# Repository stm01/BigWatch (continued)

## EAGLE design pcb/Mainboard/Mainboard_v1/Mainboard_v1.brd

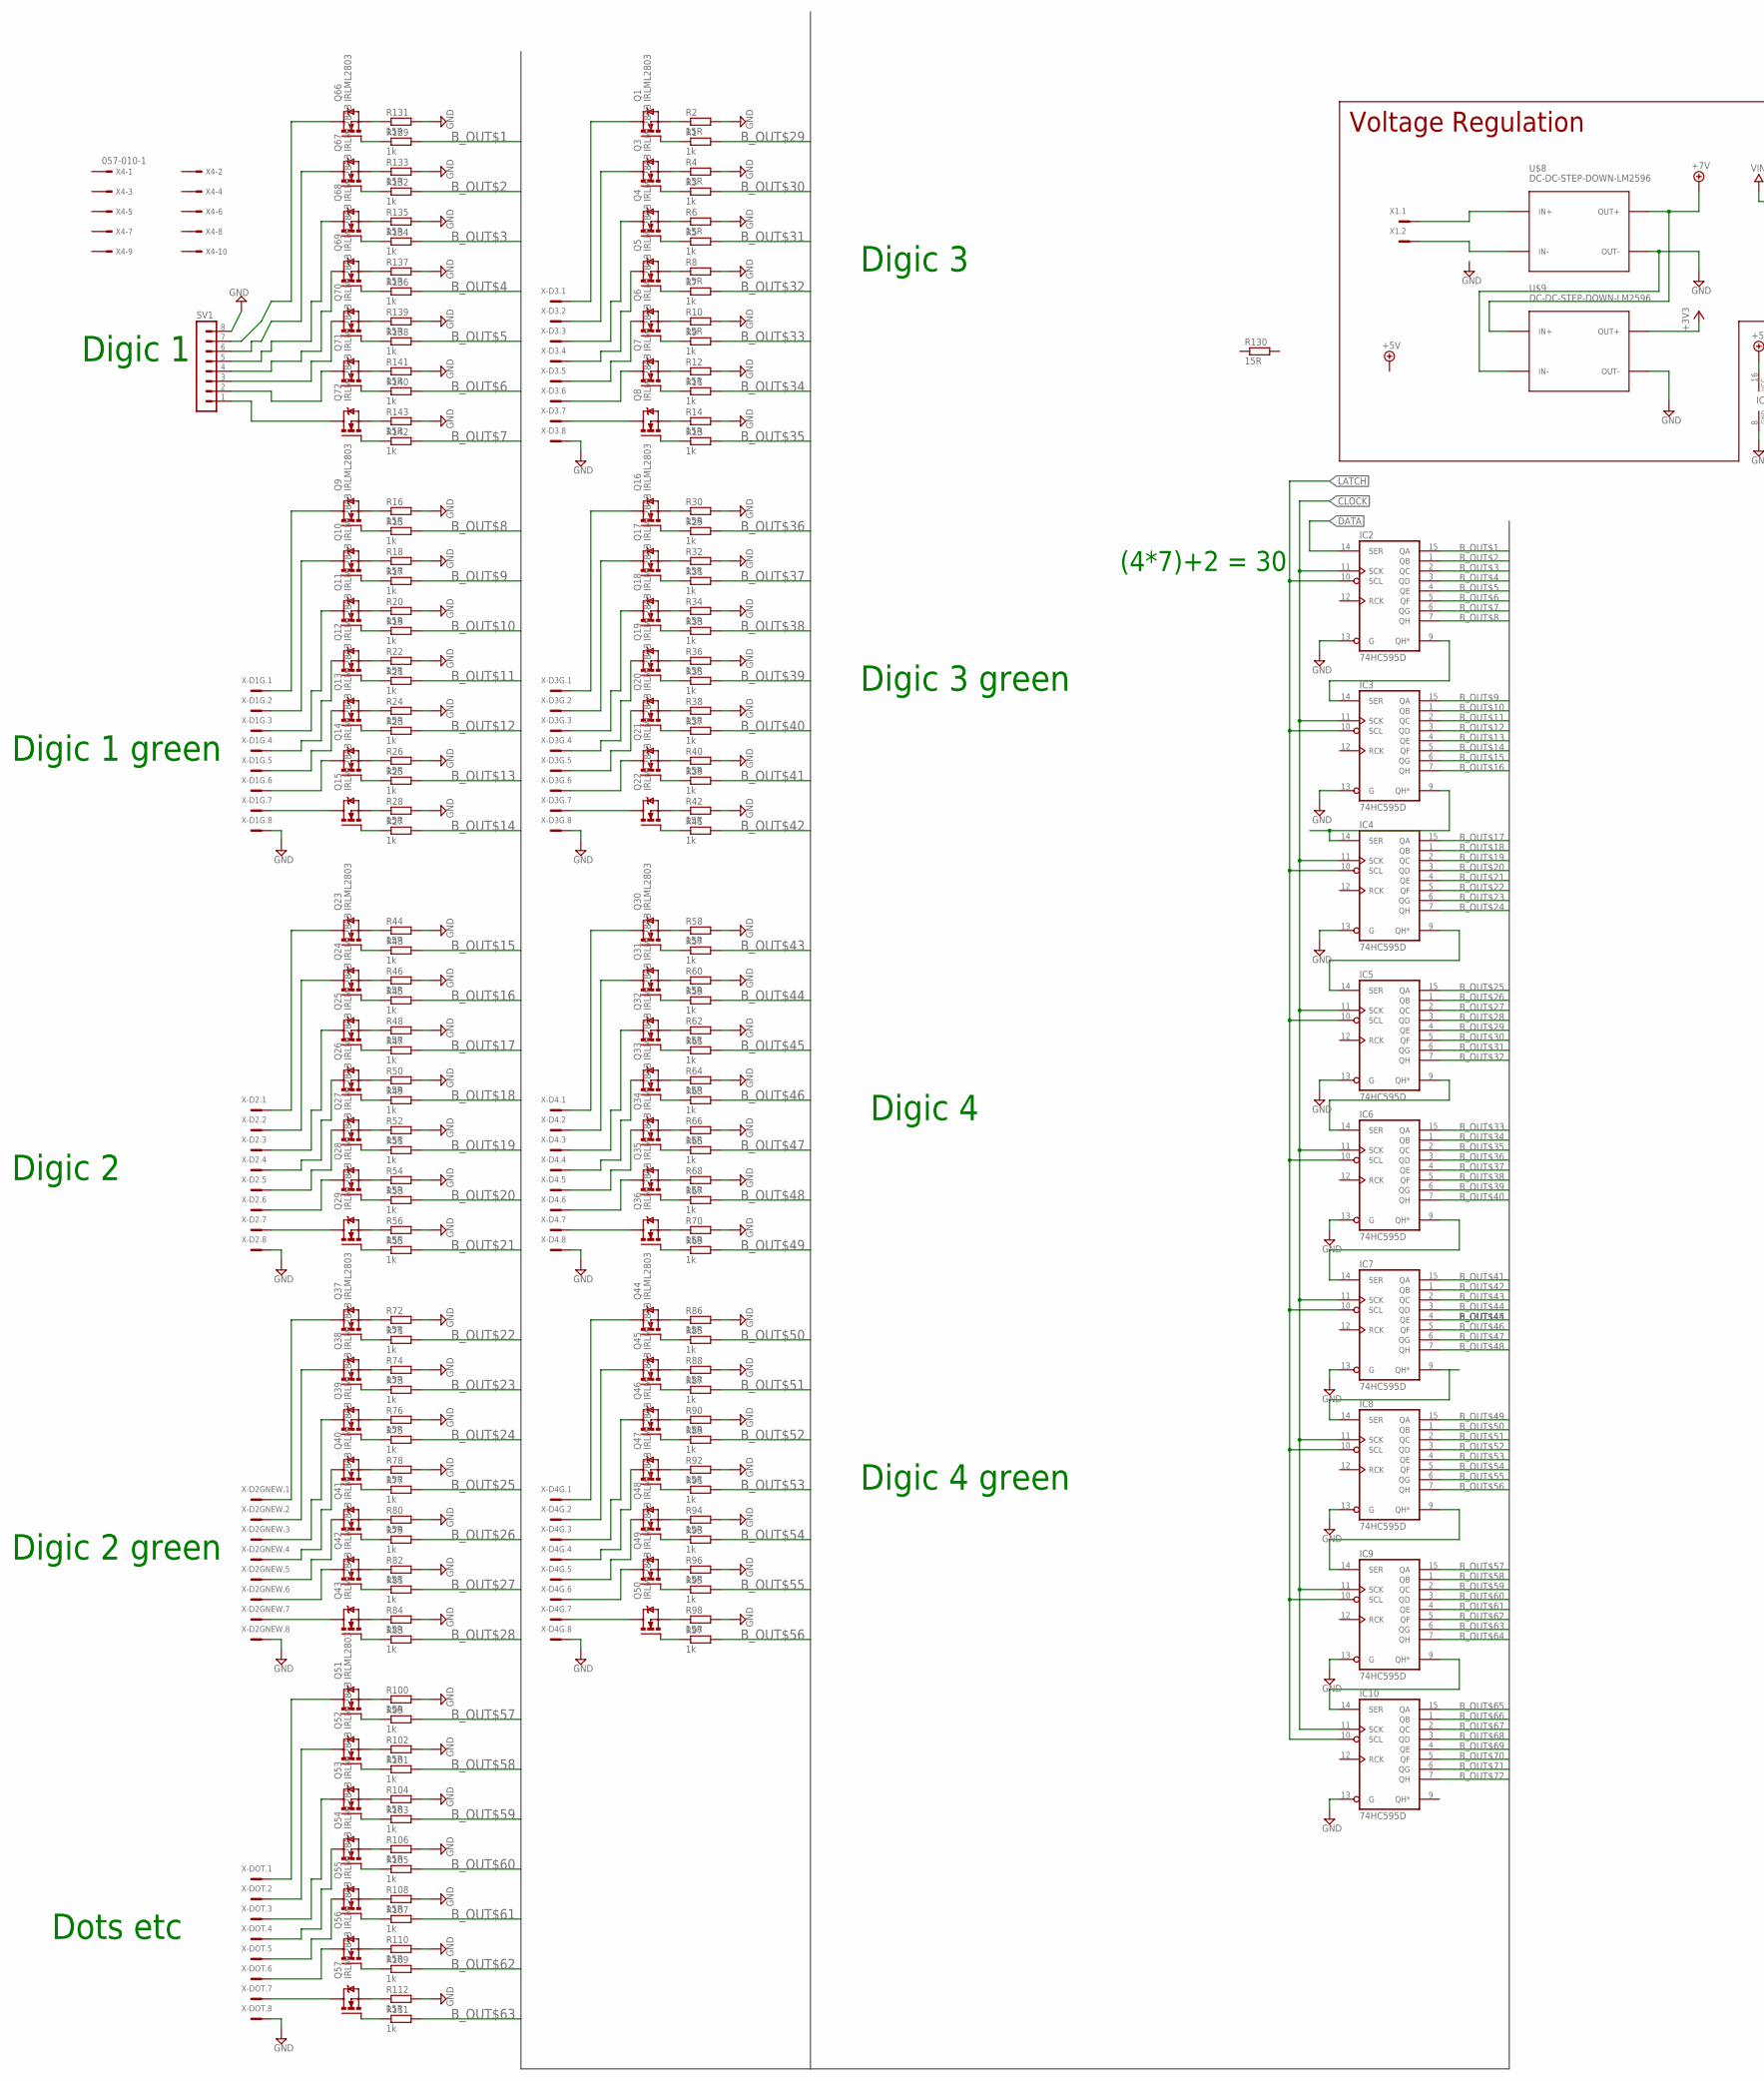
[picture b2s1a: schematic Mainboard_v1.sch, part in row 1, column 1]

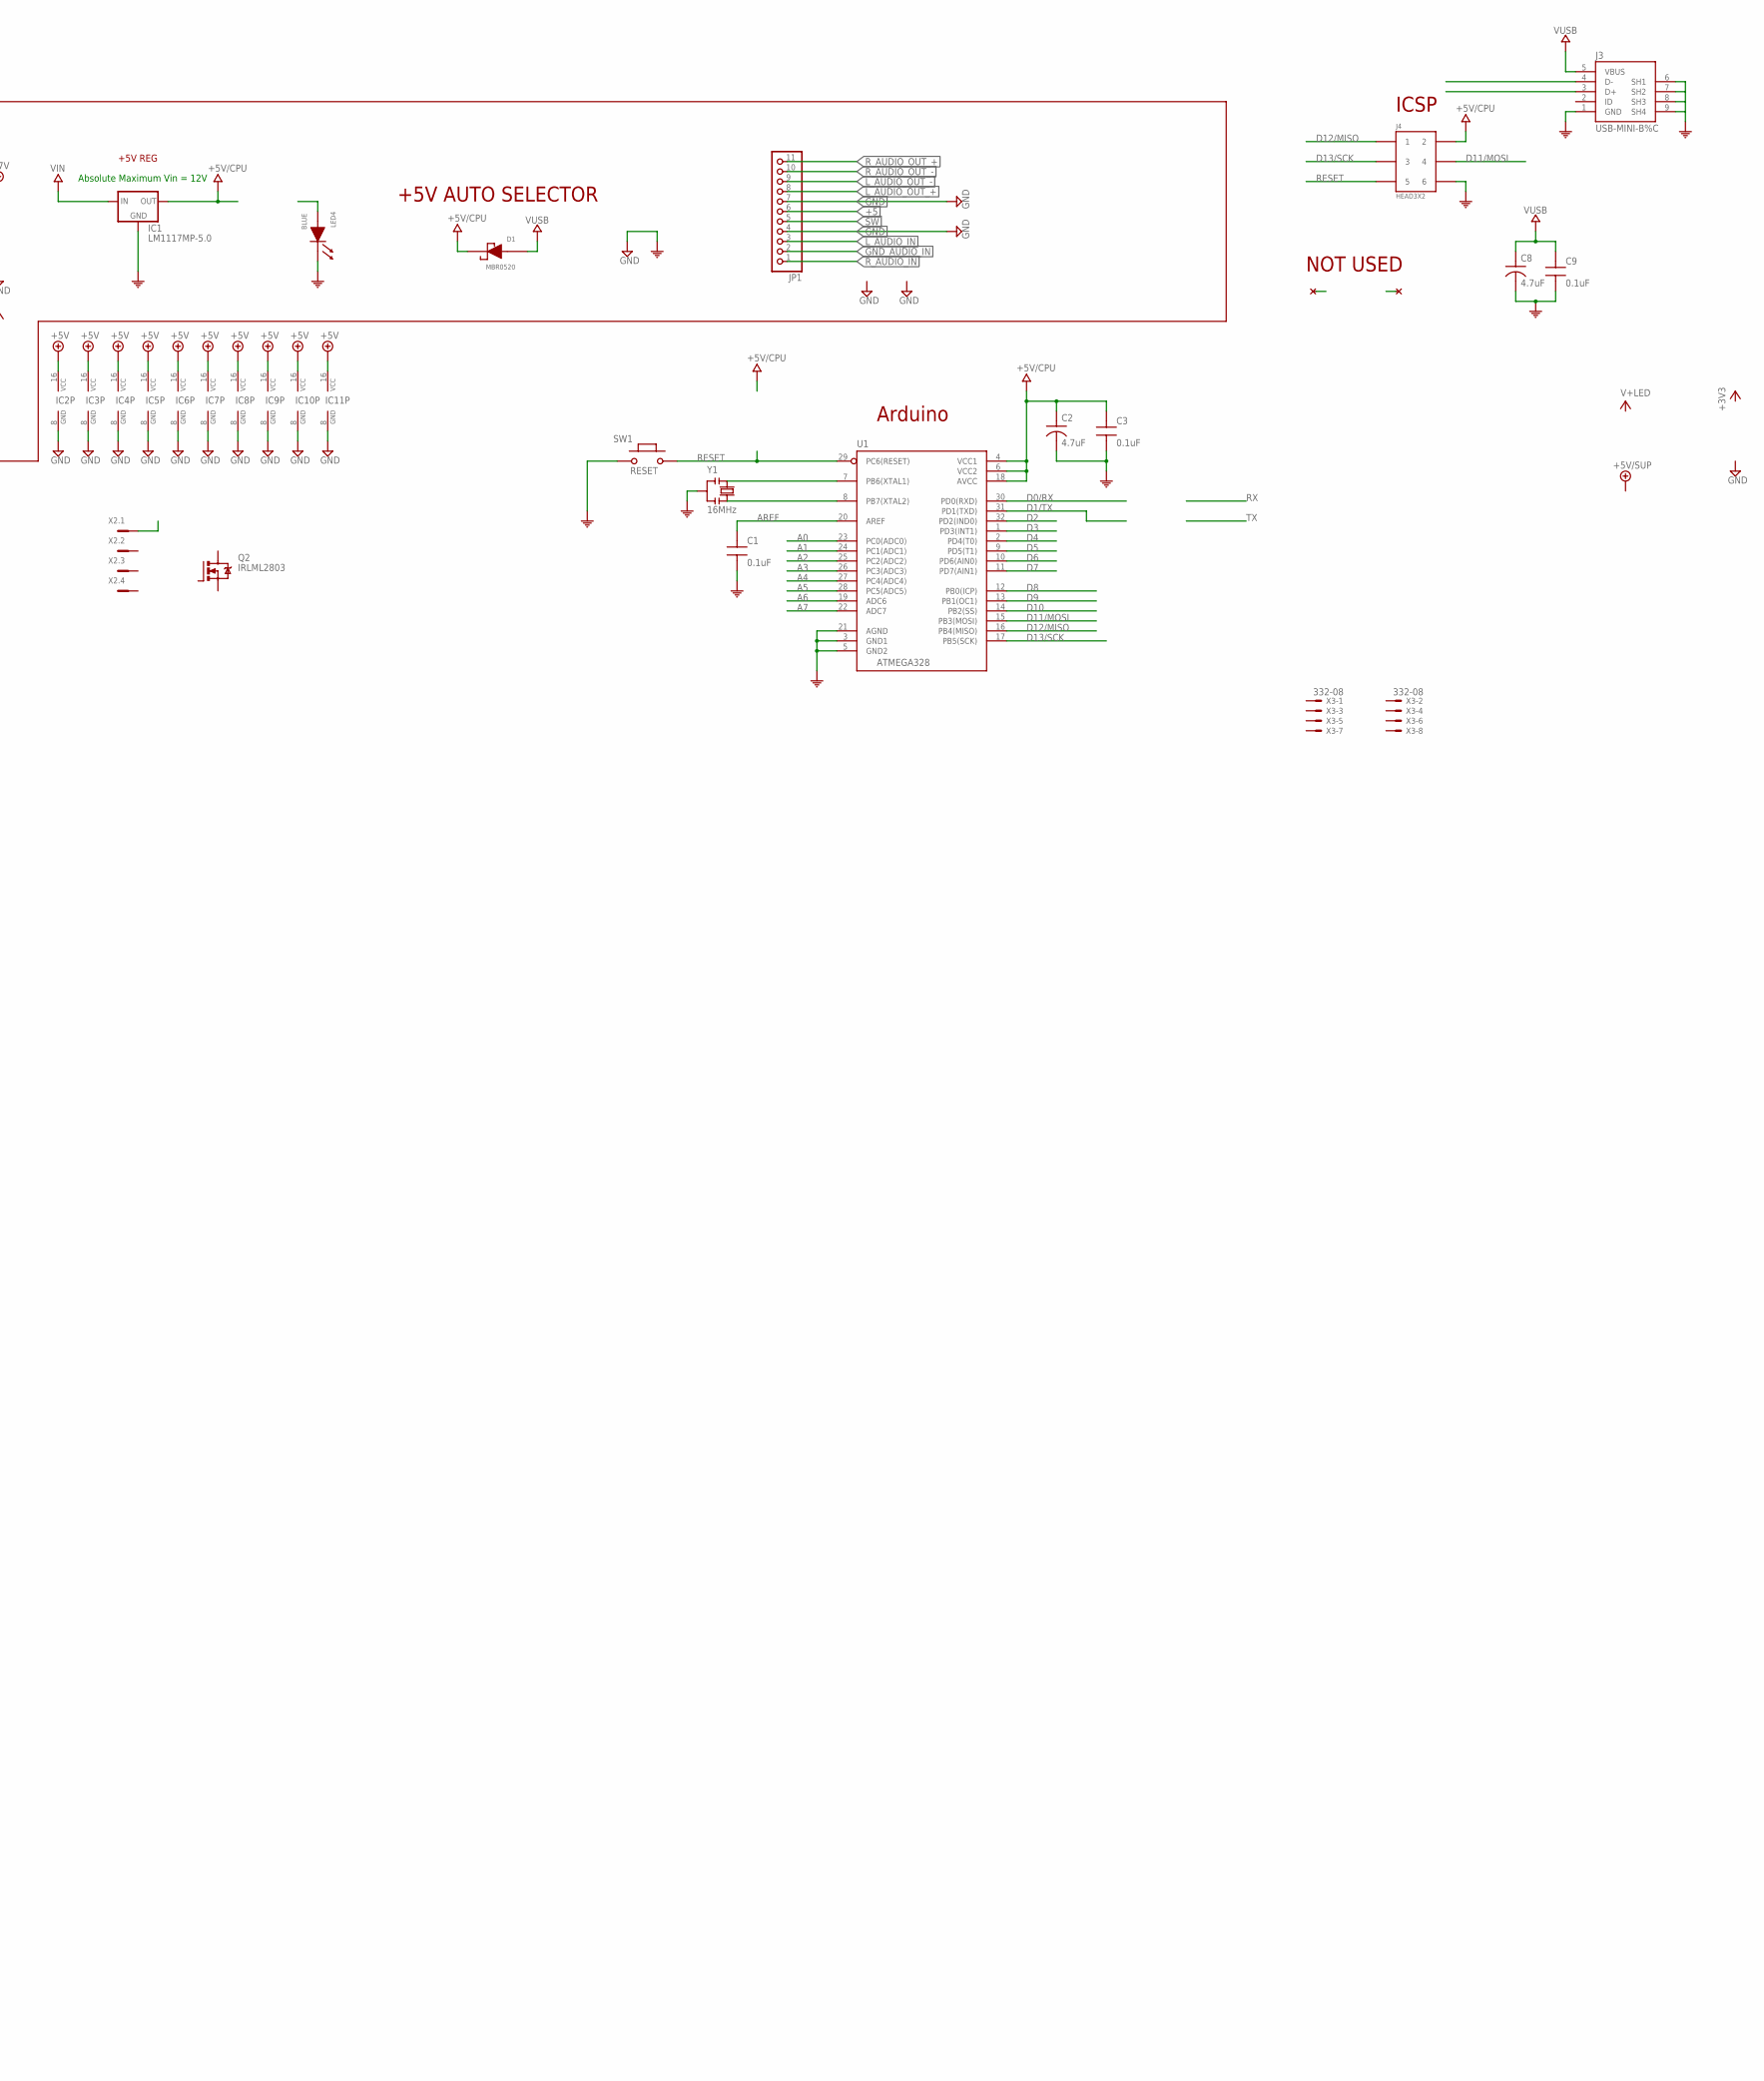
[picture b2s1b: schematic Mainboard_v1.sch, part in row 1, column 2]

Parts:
C1, C3, C9: 0.1uF; CAP0805-NP
C2, C8: 4.7uF; TAN-A
D1: MBR0520; SOD-123
IC1: LM1117MP-5.0; SOT223
IC2, IC3, IC4, IC5, IC6, IC7, IC8, IC9, IC10, IC11: 74HC595D; SO16
J3: USB-MINI-B%C; USB-MINI-B_2
J4: HEAD3X2
JP1: PINHD-1X11_2.00; 1X11M
LED4: BLUE; LED0805
Q1, Q2, Q3, Q4, Q5, Q6, Q7, Q8, Q9, Q10, Q11, Q12, Q13, Q14, Q15, Q16, Q17, Q18, Q19, Q20, Q21, Q22, Q23, Q24, Q25, Q26, Q27, Q28, Q29, Q30, Q31, Q32, Q33, Q34, Q35, Q36, Q37, Q38, Q39, Q40, Q41, Q42, Q43, Q44, Q45, Q46, Q47, Q48, Q49, Q50, Q51, Q52, Q53, Q54, Q55, Q56, Q57, Q66, Q67, Q68, Q69, Q70, Q71, Q72: IRLML2803; MICRO3
R1, R3, R5, R7, R9, R11, R13, R15, R17, R19, R21, R23, R25, R27, R29, R31, R33, R35, R37, R39, R41, R43, R45, R47, R49, R51, R53, R55, R57, R59, R61, R63, R65, R67, R69, R71, R73, R75, R77, R79, R81, R83, R85, R87, R89, R91, R93, R95, R97, R99, R101, R103, R105, R107, R109, R111, R129, R132, R134, R136, R138, R140, R142: 1k; M0805
R2, R4, R6, R8, R10, R12, R14, R16, R18, R20, R22, R24, R26, R28, R30, R32, R34, R36, R38, R40, R42, R44, R46, R48, R50, R52, R54, R56, R58, R60, R62, R64, R66, R68, R70, R72, R74, R76, R78, R80, R82, R84, R86, R88, R90, R92, R94, R96, R98, R100, R102, R104, R106, R108, R110, R112, R130, R131, R133, R135, R137, R139, R141, R143: 15R; M1206
SV1: MA08-1W
SW1: RESET; 157SW
U1: ATMEGA328; QFP032
U$8, U$9: DC-DC-STEP-DOWN-LM2596
X1: MCV2-LOCK
X2: MCV4-LOCK
X3: 332-08
X4: 057-010-1
X-D1G, X-D2, X-D2GNEW, X-D3, X-D3G, X-D4, X-D4G: MCV8-LOCK
X-DOT: MCV8-LOCK
Y1: 16MHz; RESONATOR

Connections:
+3V3: U$9.OUT+
+5: JP1.6
+5V: C2.1, C3.1, D1.1 (CA), IC1.2 (OUT), IC1.4 (OUT), IC2.16 (VCC), IC3.16 (VCC), IC4.16 (VCC), IC5.16 (VCC), IC6.16 (VCC), IC7.16 (VCC), IC8.16 (VCC), IC9.16 (VCC), IC10.16 (VCC), IC11.16 (VCC), J4.2, U1.4 (VCC1), U1.6 (VCC2), U1.18 (AVCC)
+7V: U$8.OUT+, U$9.IN+
A0: U1.23 (PC0(ADC0))
A1: U1.24 (PC1(ADC1))
A2: U1.25 (PC2(ADC2))
A3: U1.26 (PC3(ADC3))
A4: U1.27 (PC4(ADC4))
A5: U1.28 (PC5(ADC5))
A6: U1.19 (ADC6)
A7: U1.22 (ADC7)
AREF: C1.1, U1.20 (AREF)
B_OUT$1: IC2.15 (QA), R129.2
B_OUT$2: IC2.1 (QB), R132.2
B_OUT$3: IC2.2 (QC), R134.2
B_OUT$4: IC2.3 (QD), R136.2
B_OUT$5: IC2.4 (QE), R138.2
B_OUT$6: IC2.5 (QF), R140.2
B_OUT$7: IC2.6 (QG), R142.2
B_OUT$8: IC2.7 (QH), R15.2
B_OUT$9: IC3.15 (QA), R17.2
B_OUT$10: IC3.1 (QB), R19.2
B_OUT$11: IC3.2 (QC), R21.2
B_OUT$12: IC3.3 (QD), R23.2
B_OUT$13: IC3.4 (QE), R25.2
B_OUT$14: IC3.5 (QF), R27.2
B_OUT$15: IC3.6 (QG), R43.2
B_OUT$16: IC3.7 (QH), R45.2
B_OUT$17: IC4.15 (QA), R47.2
B_OUT$18: IC4.1 (QB), R49.2
B_OUT$19: IC4.2 (QC), R51.2
B_OUT$20: IC4.3 (QD), R53.2
B_OUT$21: IC4.4 (QE), R55.2
B_OUT$22: IC4.5 (QF), R71.2
B_OUT$23: IC4.6 (QG), R73.2
B_OUT$24: IC4.7 (QH), R75.2
B_OUT$25: IC5.15 (QA), R77.2
B_OUT$26: IC5.1 (QB), R79.2
B_OUT$27: IC5.2 (QC), R81.2
B_OUT$28: IC5.3 (QD), R83.2
B_OUT$29: IC5.4 (QE), R1.2
B_OUT$30: IC5.5 (QF), R3.2
B_OUT$31: IC5.6 (QG), R5.2
B_OUT$32: IC5.7 (QH), R7.2
B_OUT$33: IC6.15 (QA), R9.2
B_OUT$34: IC6.1 (QB), R11.2
B_OUT$35: IC6.2 (QC), R13.2
B_OUT$36: IC6.3 (QD), R29.2
B_OUT$37: IC6.4 (QE), R31.2
B_OUT$38: IC6.5 (QF), R33.2
B_OUT$39: IC6.6 (QG), R35.2
B_OUT$40: IC6.7 (QH), R37.2
B_OUT$41: IC7.15 (QA), R39.2
B_OUT$42: IC7.1 (QB), R41.2
B_OUT$43: IC7.2 (QC), R57.2
B_OUT$44: IC7.3 (QD), R59.2
B_OUT$45: IC7.4 (QE), R61.2
B_OUT$46: IC7.5 (QF), R63.2
B_OUT$47: IC7.6 (QG), R65.2
B_OUT$48: IC7.7 (QH), R67.2
B_OUT$49: IC8.15 (QA), R69.2
B_OUT$50: IC8.1 (QB), R85.2
B_OUT$51: IC8.2 (QC), R87.2
B_OUT$52: IC8.3 (QD), R89.2
B_OUT$53: IC8.4 (QE), R91.2
B_OUT$54: IC8.5 (QF), R93.2
B_OUT$55: IC8.6 (QG), R95.2
B_OUT$56: IC8.7 (QH), R97.2
B_OUT$57: IC9.15 (QA), R99.2
B_OUT$58: IC9.1 (QB), R101.2
B_OUT$59: IC9.2 (QC), R103.2
B_OUT$60: IC9.3 (QD), R105.2
B_OUT$61: IC9.4 (QE), R107.2
B_OUT$62: IC9.5 (QF), R109.2
B_OUT$63: IC9.6 (QG), R111.2
B_OUT$64: IC9.7 (QH)
B_OUT$65: IC10.15 (QA)
B_OUT$66: IC10.1 (QB)
B_OUT$67: IC10.2 (QC)
B_OUT$68: IC10.3 (QD)
B_OUT$69: IC10.4 (QE)
B_OUT$70: IC10.5 (QF)
B_OUT$71: IC10.6 (QG)
B_OUT$72: IC10.7 (QH)
CLOCK: IC2.11 (SCK), IC3.11 (SCK), IC4.11 (SCK), IC5.11 (SCK), IC6.11 (SCK), IC7.11 (SCK), IC8.11 (SCK), IC9.11 (SCK), IC10.11 (SCK)
COM: C1.2, C2.2, C3.2, C8.2, C9.2, IC1.1 (GND), J3.1 (GND), J3.6 (SH1), J3.7 (SH2), J3.8 (SH3), J3.9 (SH4), J4.6, LED4.1 (CA), SW1.1, U1.3 (GND1), U1.5 (GND2), U1.21 (AGND), Y1.2
D0/RX: U1.30 (PD0(RXD))
D1/TX: U1.31 (PD1(TXD))
D2: U1.32 (PD2(IND0))
D3: U1.1 (PD3(INT1))
D4: U1.2 (PD4(T0))
D5: U1.9 (PD5(T1))
D6: U1.10 (PD6(AIN0))
D7: U1.11 (PD7(AIN1))
D8: U1.12 (PB0(ICP))
D9: U1.13 (PB1(OC1))
D10: U1.14 (PB2(SS))
D11/MOSI: J4.4, U1.15 (PB3(MOSI))
D12/MISO: J4.1, U1.16 (PB4(MISO))
D13/SCK: J4.3, U1.17 (PB5(SCK))
DATA: IC2.14 (SER)
GND: IC2.8 (GND), IC2.13 (G), IC3.8 (GND), IC3.13 (G), IC4.8 (GND), IC4.13 (G), IC5.8 (GND), IC5.13 (G), IC6.8 (GND), IC6.13 (G), IC7.8 (GND), IC7.13 (G), IC8.8 (GND), IC8.13 (G), IC9.8 (GND), IC9.13 (G), IC10.8 (GND), IC10.13 (G), IC11.8 (GND), JP1.4, JP1.7, R2.2, R4.2, R6.2, R8.2, R10.2, R12.2, R14.2, R16.2, R18.2, R20.2, R22.2, R24.2, R26.2, R28.2, R30.2, R32.2, R34.2, R36.2, R38.2, R40.2, R42.2, R44.2, R46.2, R48.2, R50.2, R52.2, R54.2, R56.2, R58.2, R60.2, R62.2, R64.2, R66.2, R68.2, R70.2, R72.2, R74.2, R76.2, R78.2, R80.2, R82.2, R84.2, R86.2, R88.2, R90.2, R92.2, R94.2, R96.2, R98.2, R100.2, R102.2, R104.2, R106.2, R108.2, R110.2, R112.2, R131.2, R133.2, R135.2, R137.2, R139.2, R141.2, R143.2, SV1.8, U$8.OUT-, U$9.IN-, U$9.OUT-, X-D1G.8, X-D2.8, X-D2GNEW.8, X-D3.8, X-D3G.8, X-D4.8, X-D4G.8, X-DOT.8
GND_AUDIO_IN: JP1.2
LATCH: IC2.10 (SCL), IC3.10 (SCL), IC4.10 (SCL), IC5.10 (SCL), IC6.10 (SCL), IC7.10 (SCL), IC8.10 (SCL), IC9.10 (SCL), IC10.10 (SCL)
L_AUDIO_IN: JP1.3
L_AUDIO_OUT_+: JP1.8
L_AUDIO_OUT_-: JP1.9
unnamed: U1.8 (PB7(XTAL2)), Y1.3
unnamed: U1.7 (PB6(XTAL1)), Y1.1
unnamed: U$8.IN+, X1.1
unnamed: U$8.IN-, X1.2
unnamed: Q1.2 (S), R2.1
unnamed: Q1.1 (G), R1.1
unnamed: IC2.9 (QH*), IC3.14 (SER)
unnamed: Q3.2 (S), R4.1
unnamed: Q3.1 (G), R3.1
unnamed: IC3.9 (QH*), IC4.14 (SER)
unnamed: Q4.2 (S), R6.1
unnamed: Q4.1 (G), R5.1
unnamed: IC5.9 (QH*), IC6.14 (SER)
unnamed: Q5.2 (S), R8.1
unnamed: Q5.1 (G), R7.1
unnamed: IC4.9 (QH*), IC5.14 (SER)
unnamed: Q6.2 (S), R10.1
unnamed: Q6.1 (G), R9.1
unnamed: IC6.9 (QH*), IC7.14 (SER)
unnamed: Q7.2 (S), R12.1
unnamed: Q7.1 (G), R11.1
unnamed: IC7.9 (QH*), IC8.14 (SER)
unnamed: Q8.2 (S), R14.1
unnamed: Q8.1 (G), R13.1
unnamed: IC8.9 (QH*), IC9.14 (SER)
unnamed: Q8.3 (D), X-D3.7
unnamed: Q7.3 (D), X-D3.6
unnamed: Q6.3 (D), X-D3.5
unnamed: Q5.3 (D), X-D3.4
unnamed: Q3.3 (D), X-D3.2
unnamed: Q1.3 (D), X-D3.1
unnamed: Q9.2 (S), R16.1
unnamed: Q9.1 (G), R15.1
unnamed: IC9.9 (QH*), IC10.14 (SER)
unnamed: Q10.2 (S), R18.1
unnamed: Q10.1 (G), R17.1
unnamed: Q11.2 (S), R20.1
unnamed: Q11.1 (G), R19.1
unnamed: Q12.2 (S), R22.1
unnamed: Q12.1 (G), R21.1
unnamed: Q13.2 (S), R24.1
unnamed: Q13.1 (G), R23.1
unnamed: Q14.2 (S), R26.1
unnamed: Q14.1 (G), R25.1
unnamed: Q15.2 (S), R28.1
unnamed: Q15.1 (G), R27.1
unnamed: Q15.3 (D), X-D1G.7
unnamed: Q14.3 (D), X-D1G.6
unnamed: Q13.3 (D), X-D1G.5
unnamed: Q12.3 (D), X-D1G.4
unnamed: Q11.3 (D), X-D1G.3
unnamed: Q10.3 (D), X-D1G.2
unnamed: Q9.3 (D), X-D1G.1
unnamed: Q16.2 (S), R30.1
unnamed: Q16.1 (G), R29.1
unnamed: Q17.2 (S), R32.1
unnamed: Q17.1 (G), R31.1
unnamed: Q18.2 (S), R34.1
unnamed: Q18.1 (G), R33.1
unnamed: Q19.2 (S), R36.1
unnamed: Q19.1 (G), R35.1
unnamed: Q20.2 (S), R38.1
unnamed: Q20.1 (G), R37.1
unnamed: Q21.2 (S), R40.1
unnamed: Q21.1 (G), R39.1
unnamed: Q22.2 (S), R42.1
unnamed: Q22.1 (G), R41.1
unnamed: Q22.3 (D), X-D3G.7
unnamed: Q21.3 (D), X-D3G.6
unnamed: Q20.3 (D), X-D3G.5
unnamed: Q19.3 (D), X-D3G.4
unnamed: Q18.3 (D), X-D3G.3
unnamed: Q17.3 (D), X-D3G.2
unnamed: Q16.3 (D), X-D3G.1
unnamed: Q23.2 (S), R44.1
unnamed: Q23.1 (G), R43.1
unnamed: Q24.2 (S), R46.1
unnamed: Q24.1 (G), R45.1
unnamed: Q25.2 (S), R48.1
unnamed: Q25.1 (G), R47.1
unnamed: Q26.2 (S), R50.1
unnamed: Q26.1 (G), R49.1
unnamed: Q27.2 (S), R52.1
unnamed: Q27.1 (G), R51.1
unnamed: Q28.2 (S), R54.1
unnamed: Q28.1 (G), R53.1
unnamed: Q29.2 (S), R56.1
unnamed: Q29.1 (G), R55.1
unnamed: Q29.3 (D), X-D2.7
unnamed: Q28.3 (D), X-D2.6
unnamed: Q27.3 (D), X-D2.5
unnamed: Q26.3 (D), X-D2.4
unnamed: Q25.3 (D), X-D2.3
unnamed: Q24.3 (D), X-D2.2
unnamed: Q23.3 (D), X-D2.1
unnamed: Q30.2 (S), R58.1
unnamed: Q30.1 (G), R57.1
unnamed: Q31.2 (S), R60.1
unnamed: Q31.1 (G), R59.1
unnamed: Q32.2 (S), R62.1
unnamed: Q32.1 (G), R61.1
unnamed: Q33.2 (S), R64.1
unnamed: Q33.1 (G), R63.1
unnamed: Q34.2 (S), R66.1
unnamed: Q34.1 (G), R65.1
unnamed: Q35.2 (S), R68.1
unnamed: Q35.1 (G), R67.1
unnamed: Q36.2 (S), R70.1
unnamed: Q36.1 (G), R69.1
unnamed: Q36.3 (D), X-D4.7
unnamed: Q35.3 (D), X-D4.6
unnamed: Q34.3 (D), X-D4.5
unnamed: Q33.3 (D), X-D4.4
unnamed: Q32.3 (D), X-D4.3
unnamed: Q31.3 (D), X-D4.2
unnamed: Q30.3 (D), X-D4.1
unnamed: Q37.2 (S), R72.1
unnamed: Q37.1 (G), R71.1
unnamed: Q38.2 (S), R74.1
unnamed: Q38.1 (G), R73.1
unnamed: Q39.2 (S), R76.1
unnamed: Q39.1 (G), R75.1
unnamed: Q40.2 (S), R78.1
unnamed: Q40.1 (G), R77.1
unnamed: Q41.2 (S), R80.1
unnamed: Q41.1 (G), R79.1
unnamed: Q42.2 (S), R82.1
unnamed: Q42.1 (G), R81.1
unnamed: Q43.2 (S), R84.1
unnamed: Q43.1 (G), R83.1
unnamed: Q43.3 (D), X-D2GNEW.7
unnamed: Q42.3 (D), X-D2GNEW.6
unnamed: Q41.3 (D), X-D2GNEW.5
unnamed: Q40.3 (D), X-D2GNEW.4
unnamed: Q39.3 (D), X-D2GNEW.3
unnamed: Q38.3 (D), X-D2GNEW.2
unnamed: Q37.3 (D), X-D2GNEW.1
unnamed: Q44.2 (S), R86.1
unnamed: Q44.1 (G), R85.1
unnamed: Q45.2 (S), R88.1
unnamed: Q45.1 (G), R87.1
unnamed: Q46.2 (S), R90.1
unnamed: Q46.1 (G), R89.1
unnamed: Q47.2 (S), R92.1
unnamed: Q47.1 (G), R91.1
unnamed: Q48.2 (S), R94.1
unnamed: Q48.1 (G), R93.1
unnamed: Q49.2 (S), R96.1
unnamed: Q49.1 (G), R95.1
unnamed: Q50.2 (S), R98.1
unnamed: Q50.1 (G), R97.1
unnamed: Q50.3 (D), X-D4G.7
unnamed: Q49.3 (D), X-D4G.6
unnamed: Q48.3 (D), X-D4G.5
unnamed: Q68.2 (S), R135.1
unnamed: Q66.2 (S), R131.1
unnamed: Q66.1 (G), R129.1
unnamed: Q68.1 (G), R134.1
unnamed: Q67.2 (S), R133.1
unnamed: Q67.1 (G), R132.1
unnamed: Q69.2 (S), R137.1
unnamed: Q69.1 (G), R136.1
unnamed: Q70.2 (S), R139.1
unnamed: Q70.1 (G), R138.1
unnamed: Q71.2 (S), R141.1
unnamed: Q71.1 (G), R140.1
unnamed: Q72.2 (S), R143.1
unnamed: Q72.1 (G), R142.1
unnamed: Q72.3 (D), SV1.1
unnamed: Q71.3 (D), SV1.2
unnamed: Q70.3 (D), SV1.3
unnamed: Q69.3 (D), SV1.4
unnamed: Q68.3 (D), SV1.5
unnamed: Q67.3 (D), SV1.6
unnamed: Q66.3 (D), SV1.7
unnamed: Q47.3 (D), X-D4G.4
unnamed: Q46.3 (D), X-D4G.3
unnamed: Q45.3 (D), X-D4G.2
unnamed: Q44.3 (D), X-D4G.1
unnamed: Q51.2 (S), R100.1
unnamed: Q51.1 (G), R99.1
unnamed: Q52.2 (S), R102.1
unnamed: Q52.1 (G), R101.1
unnamed: Q53.2 (S), R104.1
unnamed: Q53.1 (G), R103.1
unnamed: Q54.2 (S), R106.1
unnamed: Q54.1 (G), R105.1
unnamed: Q55.2 (S), R108.1
unnamed: Q55.1 (G), R107.1
unnamed: Q56.2 (S), R110.1
unnamed: Q56.1 (G), R109.1
unnamed: Q57.2 (S), R112.1
unnamed: Q57.1 (G), R111.1
unnamed: Q57.3 (D), X-DOT.7
unnamed: Q56.3 (D), X-DOT.6
unnamed: Q55.3 (D), X-DOT.5
unnamed: Q54.3 (D), X-DOT.4
unnamed: Q53.3 (D), X-DOT.3
unnamed: Q52.3 (D), X-DOT.2
unnamed: Q51.3 (D), X-DOT.1
RESET: J4.5, SW1.2, U1.29 (PC6(RESET))
R_AUDIO_IN: JP1.1
R_AUDIO_OUT_+: JP1.11
R_AUDIO_OUT_-: JP1.10
SW: JP1.5
VIN: IC1.3 (IN)
VUSB: C8.1, C9.1, D1.2 (AN), J3.5 (VBUS)
X-D1G: Q4.3 (D), X-D3.3

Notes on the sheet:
Arduino
+5V REG
ICSP
+5V AUTO SELECTOR
NOT USED
Absolute Maximum Vin = 12V
Voltage Regulation
(4*7)+2 = 30
Digic 1
Digic 1 green
Digic 2 green
Digic 3 green
Digic 4 green
Digic 4
Digic 3
Dots etc
Digic 2

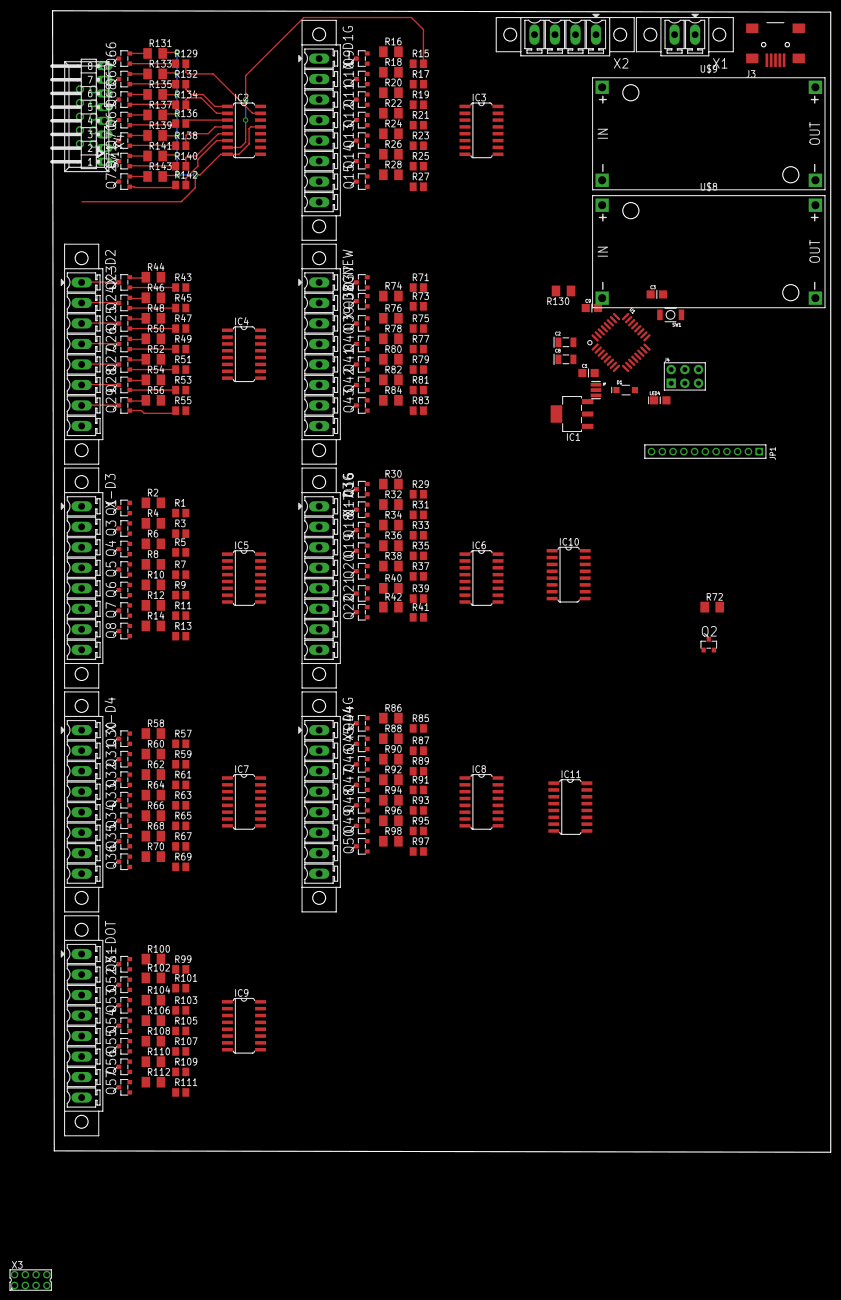
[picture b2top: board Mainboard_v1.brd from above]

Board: 2 copper layers, 144.6 x 212.1 mm, 230 parts (0 on the bottom side), 276 nets.

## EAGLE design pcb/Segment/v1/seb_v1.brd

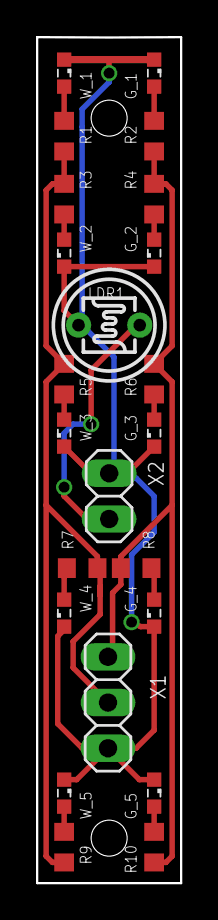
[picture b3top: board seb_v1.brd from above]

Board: 2 copper layers, 8.0 x 47.0 mm, 23 parts (0 on the bottom side), 14 nets.

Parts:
G_1, G_2, G_3, G_4, G_5: SML0603
LDR1: A1050_09; T0-46-A10XX
R1, R2, R3, R4, R5, R6, R7, R8, R9, R10: R0603
W_1, W_2, W_3, W_4, W_5: SML0603
X1: 1X03
X2: 1X02

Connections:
GND: G_1.C, G_2.C, G_3.C, G_4.C, G_5.C, LDR1.2, W_1.C, W_2.C, W_3.C, W_4.C, W_5.C, X1.1, X2.2
G_+: R2.1, R4.1, R6.1, R8.1, R10.1, X1.3
unnamed: G_1.A, R2.2
unnamed: G_2.A, R4.2
unnamed: G_3.A, R6.2
unnamed: G_4.A, R8.2
unnamed: G_5.A, R10.2
unnamed: LDR1.1, X2.1
unnamed: R1.2, W_1.A
unnamed: R3.2, W_2.A
unnamed: R5.2, W_3.A
unnamed: R7.2, W_4.A
unnamed: R9.2, W_5.A
W_+: R1.1, R3.1, R5.1, R7.1, R9.1, X1.2

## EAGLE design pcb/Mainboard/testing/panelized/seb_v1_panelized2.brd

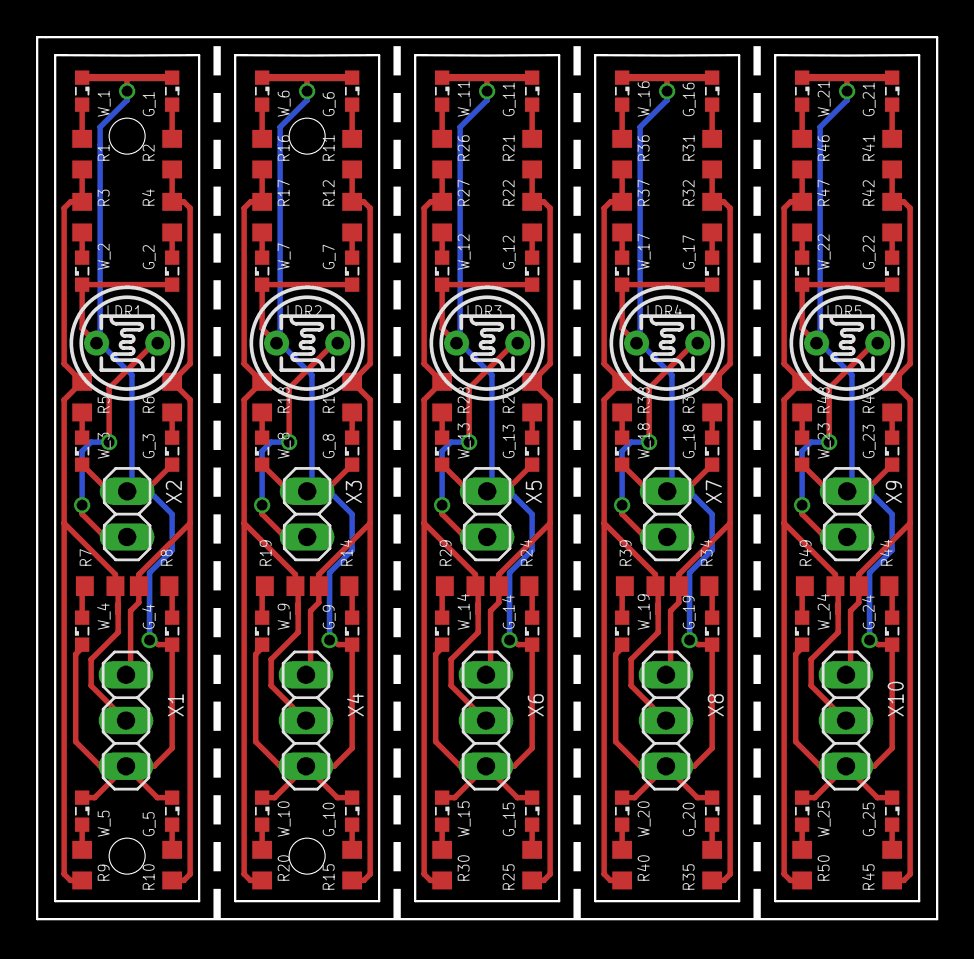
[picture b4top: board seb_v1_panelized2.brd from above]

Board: 2 copper layers, 50.0 x 49.0 mm, 115 parts (0 on the bottom side), 70 nets.

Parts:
G_1, G_2, G_3, G_4, G_5, G_6, G_7, G_8, G_9, G_10, G_11, G_12, G_13, G_14, G_15, G_16, G_17, G_18, G_19, G_20, G_21, G_22, G_23, G_24, G_25: SML0603
LDR1, LDR2, LDR3, LDR4, LDR5: A1050_09; T0-46-A10XX
R1, R2, R3, R4, R5, R6, R7, R8, R9, R10, R11, R12, R13, R14, R15, R16, R17, R18, R19, R20, R21, R22, R23, R24, R25, R26, R27, R28, R29, R30, R31, R32, R33, R34, R35, R36, R37, R38, R39, R40, R41, R42, R43, R44, R45, R46, R47, R48, R49, R50: R0603
W_1, W_2, W_3, W_4, W_5, W_6, W_7, W_8, W_9, W_10, W_11, W_12, W_13, W_14, W_15, W_16, W_17, W_18, W_19, W_20, W_21, W_22, W_23, W_24, W_25: SML0603
X1, X4, X6, X8, X10: 1X03
X2, X3, X5, X7, X9: 1X02

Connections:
GND: G_1.C, G_2.C, G_3.C, G_4.C, G_5.C, LDR1.2, W_1.C, W_2.C, W_3.C, W_4.C, W_5.C, X1.1, X2.2
GND2: G_11.C, G_12.C, G_13.C, G_14.C, G_15.C, LDR3.2, W_11.C, W_12.C, W_13.C, W_14.C, W_15.C, X5.2, X6.1
GND3: G_16.C, G_17.C, G_18.C, G_19.C, G_20.C, LDR4.2, W_16.C, W_17.C, W_18.C, W_19.C, W_20.C, X7.2, X8.1
GND4: G_21.C, G_22.C, G_23.C, G_24.C, G_25.C, LDR5.2, W_21.C, W_22.C, W_23.C, W_24.C, W_25.C, X9.2, X10.1
GND5: G_6.C, G_7.C, G_8.C, G_9.C, G_10.C, LDR2.2, W_6.C, W_7.C, W_8.C, W_9.C, W_10.C, X3.2, X4.1
G_+: R2.1, R4.1, R6.1, R8.1, R10.1, X1.3
G_+1: R11.1, R12.1, R13.1, R14.1, R15.1, X4.3
G_+2: R21.1, R22.1, R23.1, R24.1, R25.1, X6.3
G_+3: R31.1, R32.1, R33.1, R34.1, R35.1, X8.3
G_+4: R41.1, R42.1, R43.1, R44.1, R45.1, X10.3
unnamed: G_1.A, R2.2
unnamed: G_2.A, R4.2
unnamed: G_3.A, R6.2
unnamed: G_4.A, R8.2
unnamed: G_5.A, R10.2
unnamed: G_6.A, R11.2
unnamed: LDR1.1, X2.1
unnamed: G_7.A, R12.2
unnamed: R1.2, W_1.A
unnamed: R3.2, W_2.A
unnamed: R5.2, W_3.A
unnamed: R7.2, W_4.A
unnamed: R9.2, W_5.A
unnamed: G_8.A, R13.2
unnamed: G_9.A, R14.2
unnamed: G_10.A, R15.2
unnamed: R16.2, W_6.A
unnamed: R17.2, W_7.A
unnamed: R18.2, W_8.A
unnamed: R19.2, W_9.A
unnamed: R20.2, W_10.A
unnamed: LDR2.1, X3.1
unnamed: G_11.A, R21.2
unnamed: G_12.A, R22.2
unnamed: G_13.A, R23.2
unnamed: G_14.A, R24.2
unnamed: G_15.A, R25.2
unnamed: R26.2, W_11.A
unnamed: R27.2, W_12.A
unnamed: R28.2, W_13.A
unnamed: R29.2, W_14.A
unnamed: R30.2, W_15.A
unnamed: LDR3.1, X5.1
unnamed: G_16.A, R31.2
unnamed: G_17.A, R32.2
unnamed: G_18.A, R33.2
unnamed: G_19.A, R34.2
unnamed: G_20.A, R35.2
unnamed: R36.2, W_16.A
unnamed: R37.2, W_17.A
unnamed: R38.2, W_18.A
unnamed: R39.2, W_19.A
unnamed: R40.2, W_20.A
unnamed: LDR4.1, X7.1
unnamed: G_21.A, R41.2
unnamed: G_22.A, R42.2
unnamed: G_23.A, R43.2
unnamed: G_24.A, R44.2
unnamed: G_25.A, R45.2
unnamed: R46.2, W_21.A
unnamed: R47.2, W_22.A
unnamed: R48.2, W_23.A
unnamed: R49.2, W_24.A
unnamed: R50.2, W_25.A
unnamed: LDR5.1, X9.1
W_+: R1.1, R3.1, R5.1, R7.1, R9.1, X1.2
W_+1: R16.1, R17.1, R18.1, R19.1, R20.1, X4.2
W_+2: R26.1, R27.1, R28.1, R29.1, R30.1, X6.2
W_+3: R36.1, R37.1, R38.1, R39.1, R40.1, X8.2
W_+4: R46.1, R47.1, R48.1, R49.1, R50.1, X10.2

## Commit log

2016-12-12 initial release
2016-12-13 initial upload
2016-12-13 Readme updated
2016-12-13 Folder sounddata for WTV sounds added
2016-12-13 Added datasheets
2016-12-13 DCF 77 Example sketch
2016-12-13 Changelog added
2017-01-07 Includes, defines
2017-01-07 BigW
2017-01-07 Sync
2017-01-07 Docu added
2017-01-07 Schematic addes
2017-01-07 PCB & Datasheets added
2017-01-07 Drawing added
2017-01-10 Softserial testing, Datasheets added
2017-01-10 Softserial testing
2017-01-10 Datasheets added
